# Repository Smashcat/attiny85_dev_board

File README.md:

# attiny85_dev_board

This is a small prototyping board for ATTiny 25/45/85 microcontrollers. It has LEDs and buttons for the PB 0-4 outputs, plus reset button. The buttons are current limited, so that if the user switches a pin to output, then sets it high then presses a button to pull to ground, it will not damage the pin. Also added lots of GND, VCC and 3.3V connections from the onboard regulator.

The board has footprints for a standard ISP header, plus a Connect-Tag 2030 micro connector, for programming and debugging.

3D render with model download [here](https://a360.co/2ICoLCz)

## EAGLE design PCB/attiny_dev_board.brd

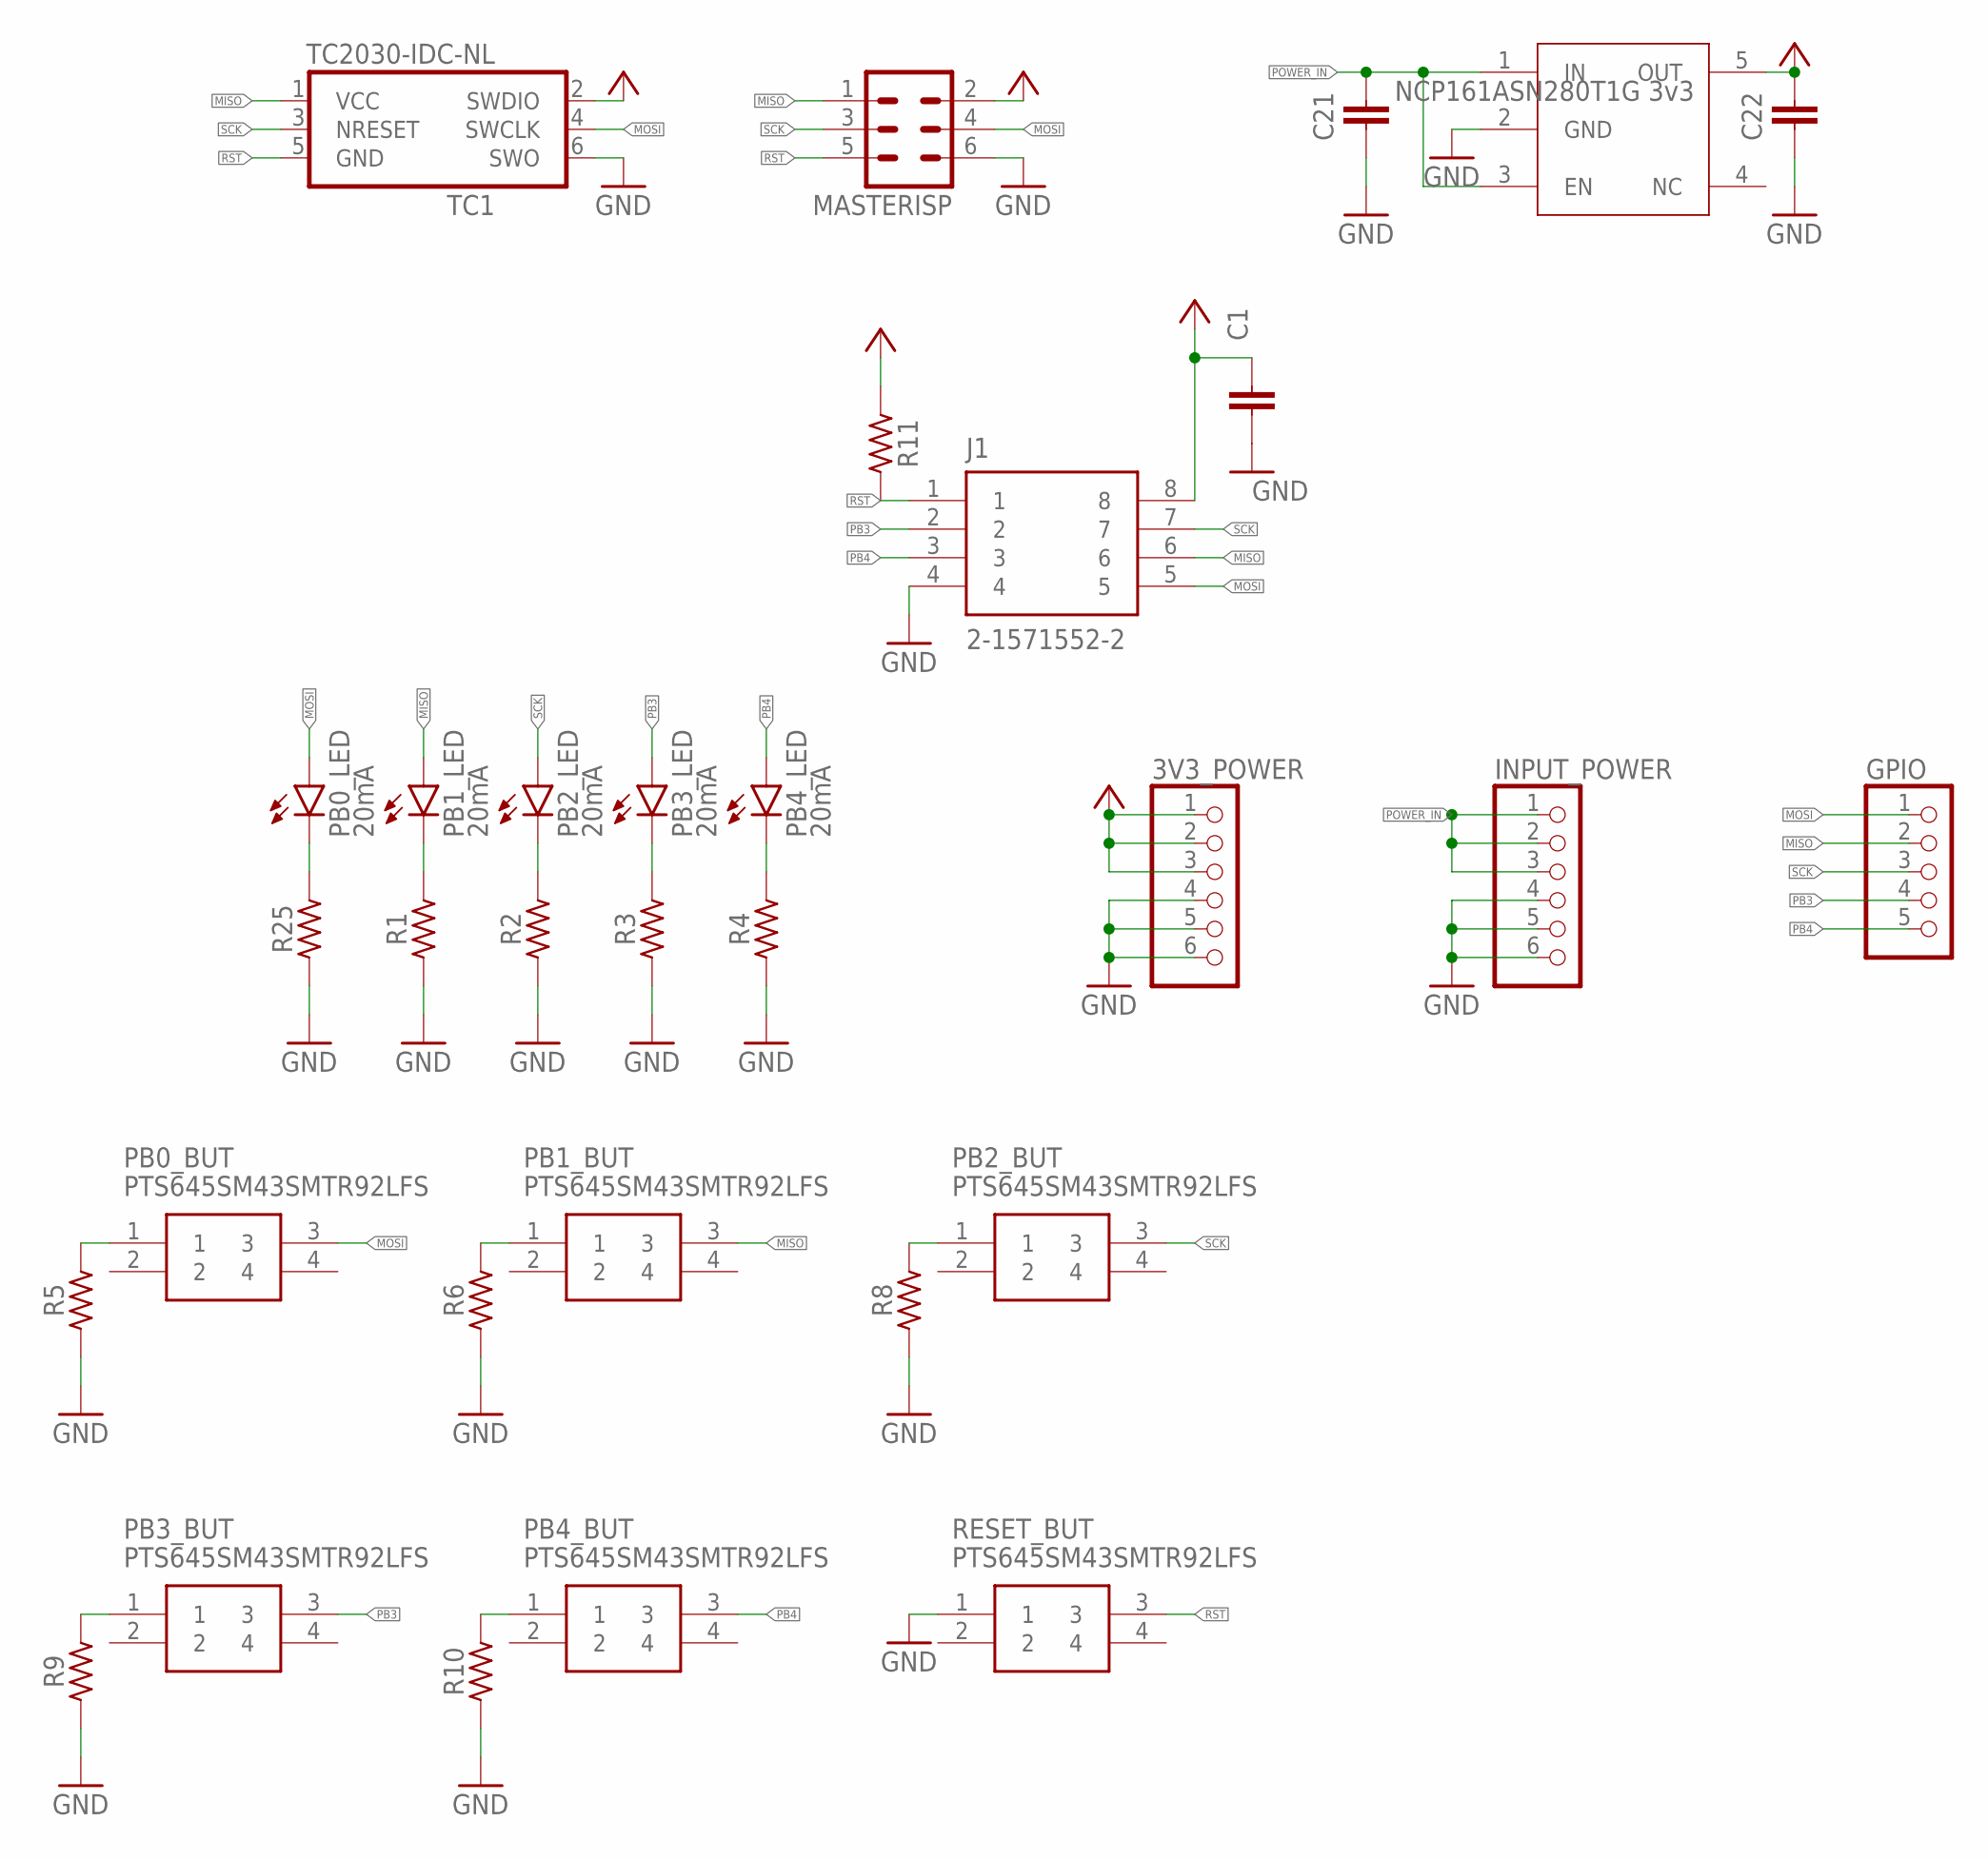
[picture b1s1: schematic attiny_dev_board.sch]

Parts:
3V3_POWER: PINHD-1X6; 1X06
3V3_REG1: 3V3; NCP718BSN330T1G
C1: 0.1uF; C0603
C21, C22: 1uF; C0603
GPIO: PINHD-1X5; 1X05
INPUT_POWER: PINHD-1X6; 1X06
J1: 2-1571552-2; TE_2-1571552-2
MASTERISP: 5v; MA03-2
PB0_BUT, PB1_BUT, PB2_BUT, PB3_BUT, PB4_BUT: PTS645SM43SMTR92LFS; PTS645(SMT)
PB0_LED, PB1_LED, PB2_LED, PB3_LED, PB4_LED: 20mA; CHIP-LED0603
R1, R2, R3, R4, R25: 1k; 52101-101-REV-A_RC-MASTER-SMD_R0603MP
R5, R6, R8, R9, R10: 20R; 52101-101-REV-A_RC-MASTER-SMD_R0603MP
R11: 10K; 52101-101-REV-A_RC-MASTER-SMD_R0603MP
RESET_BUT: PTS645SM43SMTR92LFS; PTS645(SMT)
TC1: TC2030-IDC-NL

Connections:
ACTIVITY_LED1: PB1_LED.C, R1.2
ACTIVITY_LED2: PB0_LED.C, R25.2
ACTIVITY_LED3: PB2_LED.C, R2.2
ACTIVITY_LED4: PB3_LED.C, R3.2
ACTIVITY_LED5: PB4_LED.C, R4.2
GND: 3V3_POWER.4, 3V3_POWER.5, 3V3_POWER.6, 3V3_REG1.2 (GND), C1.2, C21.2, C22.2, INPUT_POWER.4, INPUT_POWER.5, INPUT_POWER.6, J1.4, MASTERISP.6, R1.1, R2.1, R3.1, R4.1, R5.1, R6.1, R8.1, R9.1, R10.1, R25.1, RESET_BUT.1, TC1.6 (SWO)
MISO: GPIO.2, J1.6, MASTERISP.1, PB1_BUT.3, PB1_LED.A, TC1.1 (VCC)
MOSI: GPIO.1, J1.5, MASTERISP.4, PB0_BUT.3, PB0_LED.A, TC1.4 (SWCLK)
unnamed: PB0_BUT.1, R5.2
unnamed: PB1_BUT.1, R6.2
unnamed: PB2_BUT.1, R8.2
unnamed: PB3_BUT.1, R9.2
unnamed: PB4_BUT.1, R10.2
PB3: GPIO.4, J1.2, PB3_BUT.3, PB3_LED.A
PB4: GPIO.5, J1.3, PB4_BUT.3, PB4_LED.A
POWER_IN: 3V3_REG1.1 (IN), 3V3_REG1.3 (EN), C21.1, INPUT_POWER.1, INPUT_POWER.2, INPUT_POWER.3
RST: J1.1, MASTERISP.5, R11.2, RESET_BUT.3, TC1.5 (GND)
SCK: GPIO.3, J1.7, MASTERISP.3, PB2_BUT.3, PB2_LED.A, TC1.3 (NRESET)
VCC: 3V3_POWER.1, 3V3_POWER.2, 3V3_POWER.3, 3V3_REG1.5 (OUT), C1.1, C22.1, J1.8, MASTERISP.2, R11.1, TC1.2 (SWDIO)

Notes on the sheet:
NCP161ASN280T1G 3v3

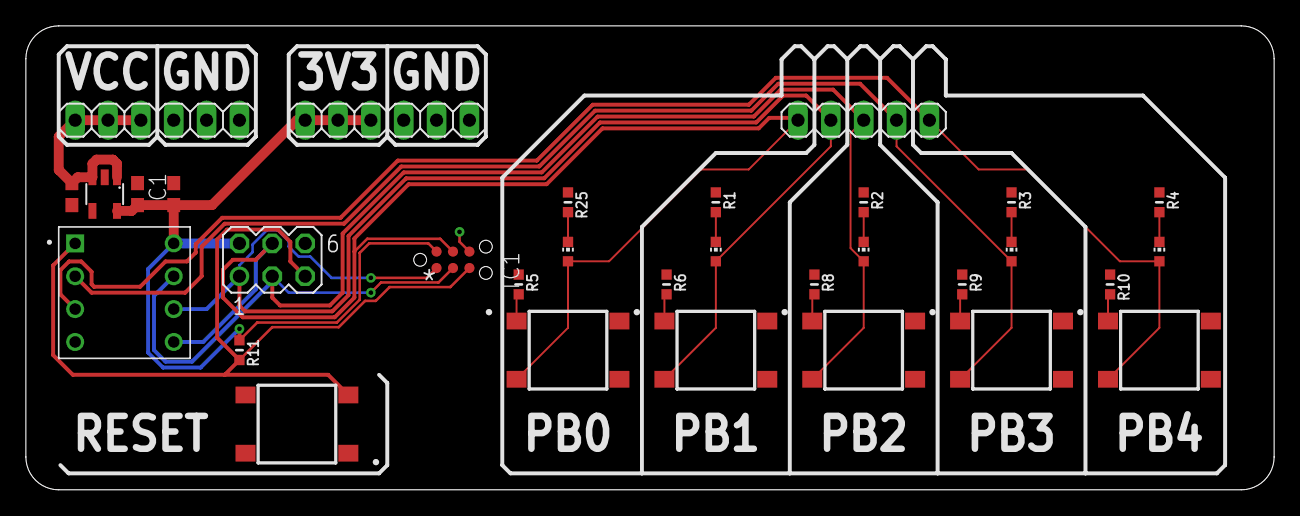
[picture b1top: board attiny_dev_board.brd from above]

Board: 2 copper layers, 96.5 x 35.9 mm, 32 parts (0 on the bottom side), 19 nets.

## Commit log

2020-11-15 Added files
2020-11-15 Added image of board
2020-11-23 Change to silkscreen
